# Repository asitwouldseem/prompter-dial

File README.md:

# prompter-dial
Use a rotary encoder to control your prompter!

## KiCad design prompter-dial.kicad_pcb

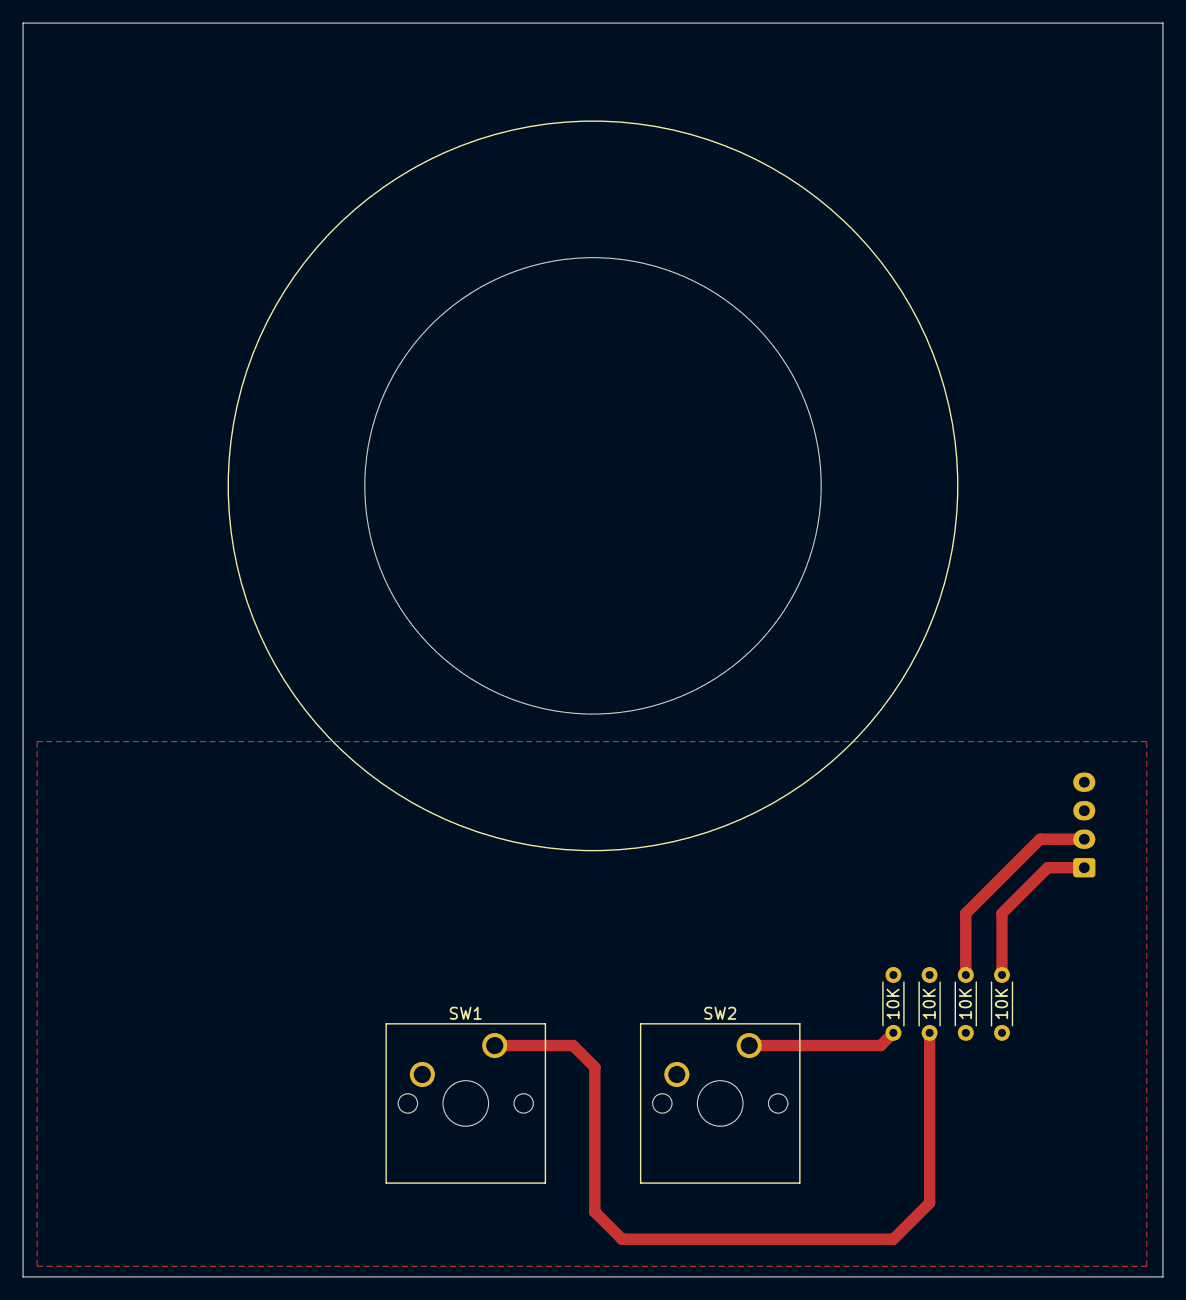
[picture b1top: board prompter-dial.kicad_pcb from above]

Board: 2 copper layers, 100.0 x 110.0 mm, 7 parts (1 on the bottom side), 6 nets.

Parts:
J1: PROMPTER WHEEL; JST_XH_B4B-XH-A_1x04_P2.50mm_Vertical
R1, R2, R5, R6: 10K; R_Axial_DIN0204_L3.6mm_D1.6mm_P5.08mm_Horizontal
SW1: JUMP; SW_Cherry_MX_1.00u_PCB
SW2: RUN; SW_Cherry_MX_1.00u_PCB

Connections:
+5V: J1.3, R5.1, R6.1, SW1.2, SW2.2
ENC_A: J1.1, R6.2
ENC_B: J1.2, R5.2
GND: J1.4, R1.2, R2.2
JUMP: R1.1, SW1.1
RUN: R2.1, SW2.1

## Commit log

2026-06-24 init
2026-06-24 Create schematic
2026-06-24 Remove caps
2026-06-24 Reduce to match available pins
2026-06-24 Add drill hole
